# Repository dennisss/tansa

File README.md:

Tansa: Dancing Robotics Platform
================================

<link rel="stylesheet" type="text/css" href="https://stackpath.bootstrapcdn.com/bootstrap/4.1.0/css/bootstrap.min.css" >

An open platform for making drones dance!

| We designed and built a 260mm quadcopter with 2 RGB spot lights and 20+ min battery life  | We have smooth transitions and minimum snap trajectories between waypoints | The controllers are optimized for high speed maneuvers
|-|-|-|
|  |  |  |

| We can seamlessly fly a whole swarm (up to 6 over WiFi) | Did I mention lights? |  Before we break our drones, we always test using our web based GUI
|-|-|-|
|  |  |  |

Overview
--------

This project includes the following:

1. Reference quadcopter electrical/mechanical designs used for developing the system
	- Around $500 BOM cost. Requires a drill, saw, 3d printer, off the shelf parts, and time to replicate.
	- Features 2 controllable spotlights for theatrical purposes
	- See `hardware/` directory

2. Drone control algorithms and drivers
	- Written in C++ with no dependency on ROS
	- Interface to networked MAVLink vehicles
	- Trajectory generation and control
		- Control based on the paper: `Minimum Snap Trajectory Generation and Control for Quadrotors` by Daniel Mellinger and Vijay Kumar
	- Motion capture support
		- Driver for using with OptiTrack Motive 1.9.0
	- Simulation Environment Integration
		- All simulation integrations are multi-drone capable out of the box
		- Gazebo support via PX4/sitl_gazebo

3. Operator User Interface
	- HTML/JS interface based for visualizing and running scripts

License
-------

Unless otherwise specified, all current files and future contributions in this repository are distributed under the MIT License (see `LICENSE` file).

Requirements
------------

This platform was primary developed for UNIX based OSes (Linux / Mac OS X), but should be mostly compatible with Windows as well (probably won't compile on windows in it's current state though).

You can optionally skip most of this and try using one of your prebuilt Docker images (see `config/docker/` directory).

For running/compiling the core code, the following libraries must be installed:

- CMake
- Eigen3
- Boost
- CGAL

For running the simulations, all dependencies on the PX4 toolchain/gazebo SITL environment must be met:
- See http://dev.px4.io/starting-installing.html
- See http://dev.px4.io/simulation-gazebo.html
	- We test with Gazebo 7

UI Dependencies
- Node.js >6.0.0
- A recent web browser such as Google Chrome that supports WebGL

Recommended/Optional Dependencies:
- The IBM CPLEX library is a recommended addition if you are using advanced trajectory generation. It is required for making collision free trajectories. If not included, it will fallback to the less stable CGAL solvers when possible.

Building
--------

1. Run `make build` to compile all the core libraries

2. Run `make build_firmware` to build the nested PX4 code and all code needed for Gazebo simulation

3. Run `npm install` to download packages needed for the GUI

Alternatively, run `make sim` to start up a multidrone simulator

Run `make run` to build the core stuff and start up the controller. Make sure that config.json has the right filepaths, and the right ip addresses if not using simulator.

Running
-------

Once everything is built, you can run `./start.sh` to quick start into a simulator with the UI running.

The script does three things

1. Starts the main gcs program via `make run`
	- This communicates and controls the drones

2. Starts the simulator using `make runSim`

3. Serves the UI via `make server`

UI
--

Viewable at `http://127.0.0.1:4000` after starting the server

- The root url will take you to the web-based 3d viewer and control suite

- Each 'choreography' is available to load and correspondences to files in the `data/` folder

- Upon loading a file, the drones should automatically spawn into the environment

Documentation
-------------

See the `doc` folder

A full source code documentation page can be generated by running `make doc`. Then the documentation can be viewed from `/build_doc/html/index.html`

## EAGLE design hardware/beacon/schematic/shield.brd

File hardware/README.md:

Hardware
========

This folder contains contains the BOMs, CAD designs, and other related notes on the open designs we developed for running with this project.

Highlights:

- `x340`
	- Our version 1 workhorse. Slightly larger than a DJI F330

- `x260`
	- Our version 2 middle size dancing drone. Half the weight of the `x340` and sports over a 3:1 power to weight ratio and over 15-25 minutes of hover time depending on the configuration.

These are made to run with our custom curated version of `PX4/Firmware`. You can find it in `lib/Firmware/` in this repository. Reflash your Pix- board with it and set the airframe number to the name of the drone (240 or 340) when calibrating in QGroundControl

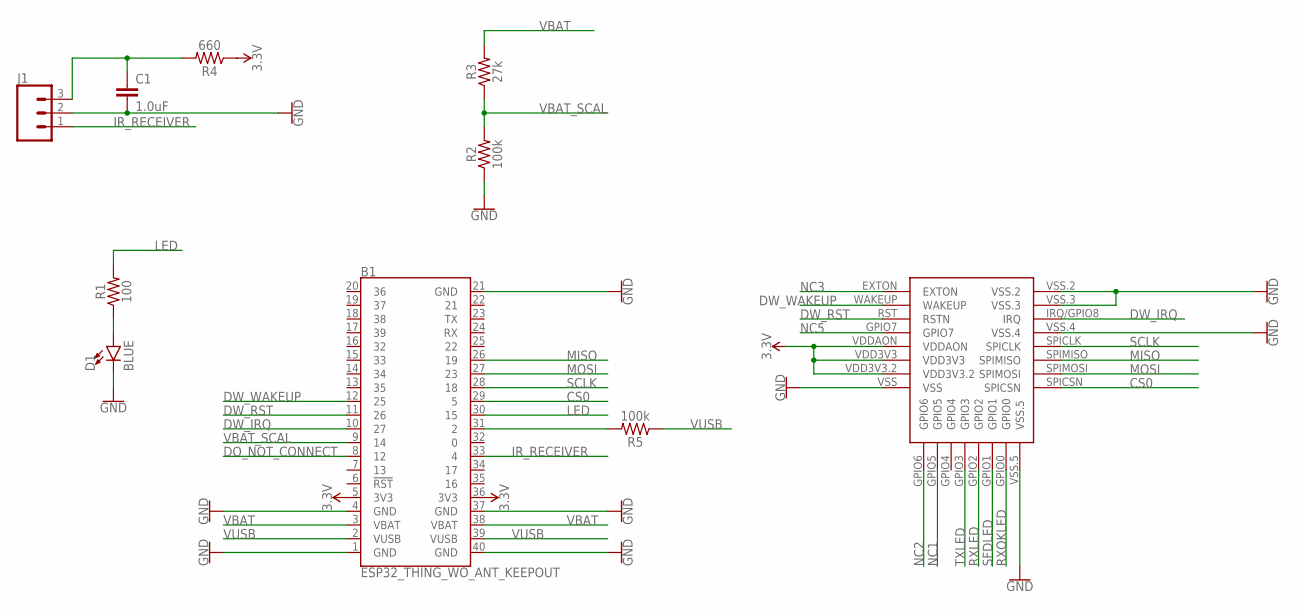
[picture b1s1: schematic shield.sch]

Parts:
B1: ESP32_THING_WO_ANT_KEEPOUT; ESP32_THING_NO_ANT
C1: 1.0uF; 1206
D1: BLUE; LED-1206
J1: CONN_03; 1X03
R1: 100; 1206
R2, R5: 100k; 1206
R3: 27k; 1206
R4: 660; 1206
U$1: DWM1000

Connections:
3.3V: B1.5 (3V3), B1.36 (3V3), R4.1, U$1.VDD3V3, U$1.VDD3V3.2, U$1.VDDAON
CS0: B1.29 (5), U$1.SPICSN
DO_NOT_CONNECT: B1.8 (12)
DW_IRQ: B1.10 (27), U$1.IRQ/GPIO8 (IRQ)
DW_RST: B1.11 (26), U$1.RST (RSTN)
DW_WAKEUP: B1.12 (25), U$1.WAKEUP
GND: B1.1 (GND), B1.4 (GND), B1.21 (GND), B1.37 (GND), B1.40 (GND), C1.2, D1.C, J1.2, R2.1, U$1.VSS, U$1.VSS.2, U$1.VSS.3, U$1.VSS.4, U$1.VSS.5
IR_RECEIVER: B1.33 (4), J1.1
LED: B1.30 (15), R1.2
MISO: B1.26 (19), U$1.SPIMISO
MOSI: B1.27 (23), U$1.SPIMOSI
unnamed: C1.1, J1.3, R4.2
unnamed: D1.A, R1.1
unnamed: B1.31 (2), R5.2
NC1: U$1.GPIO5
NC2: U$1.GPIO6
NC3: U$1.EXTON
NC5: U$1.GPIO7
RXLED: U$1.GPIO2
RXOKLED: U$1.GPIO0
SCLK: B1.28 (18), U$1.SPICLK
SFDLED: U$1.GPIO1
TXLED: U$1.GPIO3
VBAT: B1.3 (VBAT), B1.38 (VBAT), R3.2
VBAT_SCAL: B1.9 (14), R2.2, R3.1
VUSB: B1.2 (VUSB), B1.39 (VUSB), R5.1

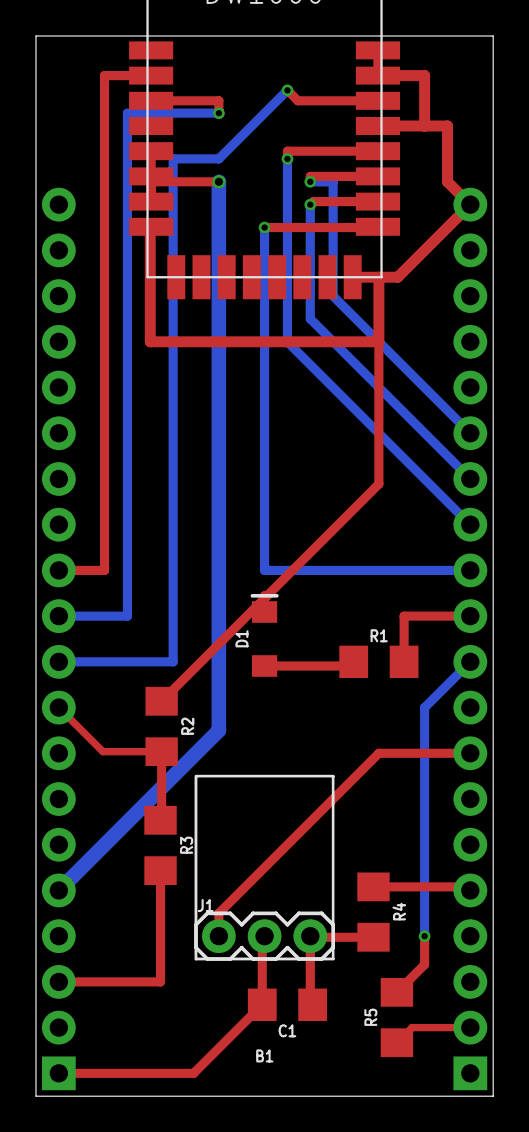
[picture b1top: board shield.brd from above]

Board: 2 copper layers, 25.4 x 58.9 mm, 10 parts (0 on the bottom side), 17 nets.

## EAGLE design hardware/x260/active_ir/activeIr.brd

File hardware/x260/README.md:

260mm X Quadcopter Design
=========================

Parts List
----------

- 4 of 138mm (length), 5mm (diameter) solid carbon fiber rods
	- https://hobbyking.com/en_us/turnigy-h-a-l-carbon-fiber-vertical-landing-skid-rod-5mm-x-250mm-4pcs-bag.html
- 2 of SLA/SLS printed center xframes
- 4 of SLA/SLS printed motor mounts
- PixRacer v1
- ACSP5 Power Board
- 4 of T-Motor MN1806 2300KV
- AfroESC Quattro 4 in 1 ESC
- Loctite Epoxy
- 2S 1500mAh LiPo Battery
- Assorted M3 Nylon Standoffs
- FrSky XM Receiver

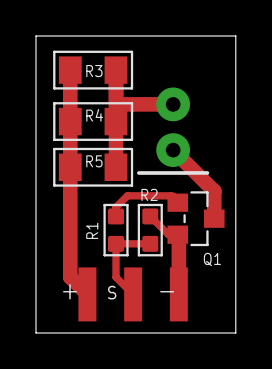
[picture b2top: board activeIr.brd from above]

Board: 2 copper layers, 11.1 x 16.5 mm, 8 parts (1 on the bottom side), 6 nets.

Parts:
D1: LED_5MM
J1: 1X03_SMD_RA_MALE
Q1: MOSFET-N; SOT-23
R1: 10; R0603
R2: 100K; R0603
R3, R4, R5: 100; R1206

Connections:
GND: J1.3, Q1.2, R2.1
unnamed: D1.K, Q1.3
unnamed: Q1.1, R1.2
unnamed: D1.A, R3.1, R4.1, R5.2
SIGNAL: J1.2, R1.1, R2.2
VCC: J1.1, R3.2, R4.2, R5.1

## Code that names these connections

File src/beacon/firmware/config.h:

/**
 * This ranges from 1-15 and a unique number should be programmed to every distinct anchor device
 * This is used as the address of this beacon
 */
const uint8_t BEACON_ID = 1;

// Enable this whenever using this in public
// This will prevent the controller from exiting anchor mode via an IR remote command
const bool ANCHOR_LOCK = false;



// NOTE: On the ESP32 Thing, VUSB is pulled down by a 10K resistor

// Used to sense when the battery is charging (this is active high)
// on the Sparkfun board, VUSB is conveniently pulled down by a 10k so we don't need any internal pulls on this
const uint8_t PIN_VBAT_SCAL = 14; // V = 0.787*Vbat  +/- 1%  (V = 0 when no battery is connected)
const uint8_t PIN_LED = 15;
const uint8_t PIN_VUSB = 2; // High if connected
const uint8_t PIN_IR_RCV = 4; // (this is active low and is pulled up in the receiver)
const uint8_t PIN_DW_WAKEUP = 25;
const uint8_t PIN_DW_RST = 26; // reset pin
const uint8_t PIN_DW_IRQ = 27; // irq pin
const uint8_t PIN_DW_SS = 5; // spi select pin

// Based on this remote: https://learn.sparkfun.com/tutorials/ir-control-kit-hookup-guide?_ga=2.140662258.1359352254.1508469480-972263269.1469291776
const uint32_t CODE_MASK = 0x10ef0000;
const uint32_t CODE_POWER = 0xd827; // PWR button, turns on configuration mode
const uint32_t CODE_A = 0xf807; // Turns on anchor mode
const uint32_t CODE_B = 0x7887; // Turns off everything
const uint32_t CODE_C = 0x58a7; // Turns on configuration/tag mode
const uint32_t CODE_CENTER = 0x20df;
const uint32_t CODE_LEFT = 0x10ef;
const uint32_t CODE_UP = 0xa05f;
const uint32_t CODE_RIGHT = 0x807f;
const uint32_t CODE_DOWN = 0x00ff;

const uint8_t NLED_PHASES = 8; // Number of LED phases per second (where each phase is a distinct high low value)
const uint8_t LED_CHARGING = 0b11000000;
const uint8_t LED_CONFIGURING = 0b1001000;
const uint8_t LED_CHARGED = 0b11111111;
const uint8_t LED_ANCHOR = 0b11111111;
const uint8_t LED_INIT = 0b10101010;

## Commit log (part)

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2016-11-12 Fixed up more of the choreography. Also added checking for discontinuities in jocs files. Throw runtime exceptions with helpful messages if discontinuity detected.
2016-11-12 Fixed a memleak with the exceptions I was throwing
2016-11-12 Made error messages for time discontinuity better
2016-11-12 Add comments for blocking sheets
2016-11-12 Candidate Interface for jocsPlayer class.
2016-11-13 Fixed up through BS11, still debugging BS12 where the circle is
2016-11-13 Moved destructor implementation to .cpp file
2016-11-13 Finished BS15, the second circle
2016-11-13 Finished up through BS17, first two pdfs of blocking sheets
2016-11-13 Adding hover to end of file
2016-11-13 Changes per Zach's comment on PR
2016-11-15 Configurable network ids corresponding to ports
2016-11-15 Add updated list of drones at conversion factor 1
2016-11-15 Try to fix misunderstood coorelation betwee drone id and index in array of drones
2016-11-15 Functionality is verified now
2016-11-15 Works for 1,2,3,4 or 5 drones but not when all 6 are run at once. Need to find bug.
2016-11-15 update selected drones
2016-11-16 Finish up through 252s
2016-11-16 Done up through 300s
2016-11-16 Works well until 5:45 of choreography, when run on lab computer
2016-11-17 Finish entire choreography
2016-11-17 add headers and empty methods - doesn't compile since nothing is returned. this is just a placeholder making the methods defined in #83
2016-11-17 take out parameter for data #83
2016-11-17 Add breakpoint class
2016-11-17 Take breakpoint methods out of JocsParser so can put them in Player class instead
2016-11-17 Fill in bodies for helper methods in jocsPlayer
2016-11-18 First cut.
2016-11-18 Fix start and end times per Mike's corrections
2016-11-18 Moved mocap and gazebo out of jocsPlayer.
2016-11-18 Cleanup
2016-11-18 Decouple player from gcs
2016-11-18 Added new function for the breakpoints.
2016-11-18 Working basic lab support
2016-11-18 remove typo
2016-11-18 Add Strobe list trajectory
2016-11-18 to test on lab computer
2016-11-19 Add saving breakpoints to jocs parse
2016-11-19 Add legit landings to state machine and refactor player
2016-11-19 Fix compile time errors in parsing lights and start handling lights in Player class
2016-11-19 Fix typoes with space discontinuity
2016-11-19 Fix runtime error from deleting an action
2016-11-19 Add reading light actions in player class
2016-11-19 Adding kill switch
2016-11-19 Refs. #67, #69, #70, #71
    Added major changes the command center to allow for drones to be controlled through a server interface.
2016-11-19 test lighting with simple jocs file
2016-11-20 Light fading should work now
2016-11-20 Better hover controller
2016-11-20 add demo for single drone, multiple light actions
2016-11-20 Attempt to resume from a pause.
2016-11-20 testing files
2016-11-20 Cleaned up jocs file listing and some other related style issues
2016-11-20 Fix -0 values due to using longs
2016-11-21 Send light commands only if changed in the past 0.01s
2016-11-21 add dummy light actions in realChoreography
2016-11-21 Shorten intensity buffer, start rough choreography update to new edits
2016-11-21 add light cues to realChoreography.jocs
2016-11-21 tweak angles
2016-11-21 Resume from pausing.
2016-11-22 Fix bug where drones are sent to wrong index's home position
2016-11-22 Fix requested for pr #95
2016-11-22 Implemented basic loading of jocs file. Missing features such as starting at cue and returning target positions
2016-11-22 Updated html file with new icons and file loading changes.
2016-11-22 try fixing tornado but get spacial distoninuity when shouldn't'
2016-11-22 fix things that shouldnt be pushed
2016-11-22 change chor to have simpler version of tornado
2016-11-23 Add time updates up until when new phase was added
2016-11-23 finish all changes
2016-11-23 Updated jocs file to be fully up to date with mike's excel sheet
2016-11-24 Added scale box Hid queue box until after file is chosen (todo: show) Added CSS cases for xs
2016-11-24 Revert "Finish light choreography"
    This reverts commit d098a00ff77e5c51fec30dd7e91cb03885c234b0.
2016-11-24 Reorganize vehicle class a little
2016-11-24 Update firmware
2016-11-24 Add hover point calibration procedure
2016-11-24 Mocap thoughts
2016-11-24 Laying out some new trajectory prototypes
2016-11-24 Use hover controller for hover actions
2016-11-25 Fix strobe trajectory logic and add ability to parse strobe from jocs file
2016-11-25 Fix order of values in strobe; fix bps to be 46 'cycles' total rather than per second
2016-11-25 Update choreography to altername strobing status between the 6 drones
2016-11-25 GUI updates, make landing and pausing smarter.
2016-11-25 Return starting positions in loading response.
2016-11-26 Added in coordinates to the grid page.
2016-11-26 Change home positions to 0 height instead of 1
2016-11-26 Try one speed for all circles in cyclone
2016-11-26 fix time discontinuity
2016-11-26 Change cyclone to 3 rotations instead of 4 for demo purposes
2016-11-26 hover on edge of circle at end
2016-11-26 add bird flock
2016-11-26 add new lighting changes
2016-11-26 Made end safe, but it doesn't match the timings
2016-11-27 cap z coordinates at 10
2016-11-27 finish scaling down first part of song
2016-11-27 fix typo making 4 and 5 crash in smallchor
2016-11-27 Start externalizing dependencies for js
2016-11-27 finish through end of song
2016-11-27 for viewing in lab comp
2016-11-27 fix discontinuity around 228
2016-11-27 Uncomment to fix.
2016-11-27 Send back adjusted start time, finished merging in master.
2016-11-27 update breakpoints to match qlab
2016-11-27 replace cyclone with a hover
2016-11-27 Fix mocap null pointer exception
2016-11-27 Update PR Template to represent master = PROD
2016-12-04 Cleaning up the gui files
2016-12-04 Remove sensitive files
2016-12-04 Add Tess’s changes from old branch (Ready to fly)
2016-12-04 Add Travis CI Integration
2016-12-04 Update Firmware Again!
2016-12-09 Forwarding of vehicle messages to/from another gcs
2017-02-10 New 260mm quad design
2017-02-10 Refactor PX4 scripts and add new vehicle methods
2017-02-10 Route pose data to WebGL player
2017-02-13 Add JS data precompiler
2017-02-14 Add simulation parameters and gps sim
2017-02-19 Some integration of new sim into gcs
2017-02-19 Added more API comments for the Action classes.
2017-02-20 Adding full minsnap implementation
2017-02-20 Need more docker dependencies
2017-02-25 Simplifed the initVehicles function. Reduced code noise
2017-02-26 Add optional CPLEX dependency
2017-02-26 Fix reusing gazebo models without restarting
2017-02-27 First Cut - WIP.
2017-03-01 Colorful viewer, change angle, logging in player
2017-03-03 Started implementing a csv parser to replace jocsParser
2017-03-03 Parsing line,hover,transition,circle. Needs testing though
2017-03-04 Fixed parser to only read first drone from line and ignore others to avoid mistakes. Until we support offsets
2017-03-04 hooked up the plubming for csv
2017-03-04 Optionally compile with Gazebo and adjust node ports
2017-03-04 Back to binary meshes for web viewer
2017-03-05 Preload gazebo dependencies in docker
2017-03-05 Fixed up example data file
2017-03-05 Adding in CSS and JS fixes for material design.
2017-03-05 Ensure bootstrap-materials are applied on dyanmic elements, remove listeners when components are unbound, and other CR feedback.
2017-03-05 Adding more controls and fixing home positions in viewer
2017-03-05 Started adding new primatives. Also changed actiontype to be a scoped enum to prevent wierd namespace clashing with useless error messages
2017-03-05 Added ellipse and spiral actions
2017-03-05 Fixes #145
2017-03-05 Fix z aliasing issue in viewer
2017-03-06 Fixed some bugs with parsing new primatives
2017-03-06 Update design files
2017-03-06 Fixed issue in data file with arc. Need to use time relative to start of choreo, not start of action. Also switched off GMP in minsnap because GMP was not working with non integer values in points or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
2017-03-06 Add upload by text
2017-03-06 Support both JOCS and CSV loading as ‘Routines’
2017-03-08 Distinguish between id and track/role
2017-03-08 For now kill acts like ‘ctrl-c’
2017-03-10 NOTE: CURRENTLY NOT COMPLETE
    Added functionality for lights and strobe (white only).
2017-03-11 Slightly better documentation and add html generation
2017-03-13 Homes can now be specified like any other action
2017-03-13 Blank lines will now be skipped in csv. Can separate blocks for visual clarity
2017-03-14 Quick and dirty preview mode
2017-03-14 Build fixes
2017-03-18 Adding onboard params and cleaner NatNet addresses
2017-03-26 Adding in the arduino lighting code and timing refactor
2017-03-31 More simulation refinements
2017-03-31 Adding some WIP stuff
2017-04-03 Some tweaks from today’s runs
2017-04-05 Adding more docs
2017-04-08 More failsafes based on state data
2017-04-09 For demo
2017-04-09 More changes to custom chores
2017-04-10 Change config file names
2017-04-13 More error checking and fix csv transformed input
2017-04-13 CSV out of bounds checking and save previous values
2017-04-13 Fix simulation parameters
2017-04-13 Implemented strobe and Light, Bugs are likely
2017-04-14 updated action interface to know about light indices. Must specify one to construct a light action
2017-04-14 Fixed light, added fade
2017-04-15 Finish generalized rigid correspondence solver
2017-04-15 Fixed dynamic strobe. It now works as intended
2017-04-16 Iterate rigid body tracker and set yaw forward direction
2017-04-17 Fixes from testing and enforce single running process
2017-04-17 We now turn light off during landing. Also fixed bug with gap filling in lighting. Wasn't filling gap with lighting if there was a gap from the end of the last command to the end of the piece.
2017-04-20 Small changes to gcs
2017-04-20 Separate vehicle updating logic
2017-04-21 Adjusted parsing to take grouped tuples
2017-04-23 Support lighting while in preview mode
2017-04-24 Drop csv test files for now (until they are updated)
2017-04-27 Skip lines with empty csv fields
2017-04-28 Start of the major refactoring
2017-04-28 Fix failsafe
2017-04-30 Document adding RC to CF2
2017-05-07 Generalize gazebo spawning code
2017-05-11 Adding mocap yaw offset and turn off lighting on arm
2017-05-12 Add misalignment compensation and some of the single dot test code
2017-05-14 Fixing lighting and more failsafes
2017-05-21 Disjoint sets implementation and blob detector
2017-05-28 Reorganize CMake for mocap and add camera interfaces
2017-05-28 Compile fixes for some platforms
2017-05-28 Adding video file mocap input and configuring raspicam
2017-06-02 Further parallelization of the blob detector
2017-06-05 Import 3d graphics library
2017-06-09 Reorganizing frontend components
2017-06-10 Adding virtual mocap camera
2017-07-09 Adding beacon position optimizer
2017-09-04 Start of reconstructor code
2017-09-04 time: fix conversion
    The intention is to check if the duration is lower than a period.
    Convert both params to int64_t.
    [ 56%] Building CXX object CMakeFiles/test_tansa.dir/test/core/time.cpp.o
    In file included from /usr/include/gtest/gtest.h:1929:0,
    from /home/user/aero-src/tansa/test/core/time.cpp:1:
    /home/user/aero-src/tansa/test/core/time.cpp: In member function ‘virtual void Time_UnitDurations_Test::TestBody()’:
2017-09-04 firmware: json fix
2017-09-04 Fix json casting error for jocs
2017-09-05 Fixing camera model for OpenGL
2017-09-09 Reconstruction extended to multi-camera
2018-04-13 Add PnP solver via ceres and adjust terms
2018-04-13 Add more notes and code adjustments
2018-04-13 Ranging and stats for beacon firmware
2018-04-13 Progress on beacon firmware
2018-04-14 Add in crazy radio driver from cfbridge
2018-04-14 Some cf file reorganization

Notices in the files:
parts and their libraries:
SparkFun-Boards: Licensing: Creative Commons ShareAlike 4.0 International - https://creativecommons.org/licenses/by-sa/4.0
